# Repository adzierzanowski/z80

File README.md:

# Zilog Z80 playground

This is a scratchpad repository containing my Z80 sandbox.

## Assembler
The most interesting for other people is most probably **[an assembler](z80asm)**
written in Python.

The assembler is more-than-two-pass assembler to make code more readable than
optimized.

I've also written a 2-pass Z80 assember in C which is much faster.
[Check it out here](https://github.com/adzierzanowski/zasm).

## Z80 Minicomputer

For now the other part of the project consists of:

* a main board with 10 MHz Zilog Z80 CPU and some LEDs,
* a RAM board with two 62256 SRAM chips, 32 kiB of memory each
  and 7-segment displays showing data and address bus state,
* a CLKMOD board acting as a clock and interrupt controller.

Implying the following specs:

```
- Up to 1 MHZ Z80 CPU (because of bottleneck that is CLKMOD which will
                       be replaced with a crystal oscillator)
- 64 kiB SRAM
- No external non-volatile memory
- No IO at the moment
```

At the moment I'm developing the new IO Controller and IO device modules:
* 128x160 TFT display module,
* PS/2 keyboard input module.

In the `legacy/` directory there are some IO controller files which I used
for communicating with the CPU via serial port and low-resolution VGA output.

# Files

* `z80asm` – Python dual-syntax (i8080, Z80) assembler/disassembler module

* `busctl/` – Bus controller (and RAM Uploader)
* `clkmod/` – Clock emulator
* `fontmaker/` – Little HTML/JS utility for creating fonts
* `legacy/` – Old unused controllers
* `lib/` – ASM libraries
* `schematics/` – KiCAD schematics
* `static/` and `templates/` – Flask assets
* `tft` – TFT Display Controller

* `ctl.py` – Flask GUI for the clock emulator
* `prog.py` – Bus controller RAM programming interface
* `serialprompt.py` – Utility for fast testing of serial communication

# Resources

* https://maker.pro/pic/projects/z80-computer-project-part-1-the-cpu
* https://istvannovak.net/2018/01/25/zx-spectrum-ide-part-3-a-brief-overview-of-the-z80a-cpu/

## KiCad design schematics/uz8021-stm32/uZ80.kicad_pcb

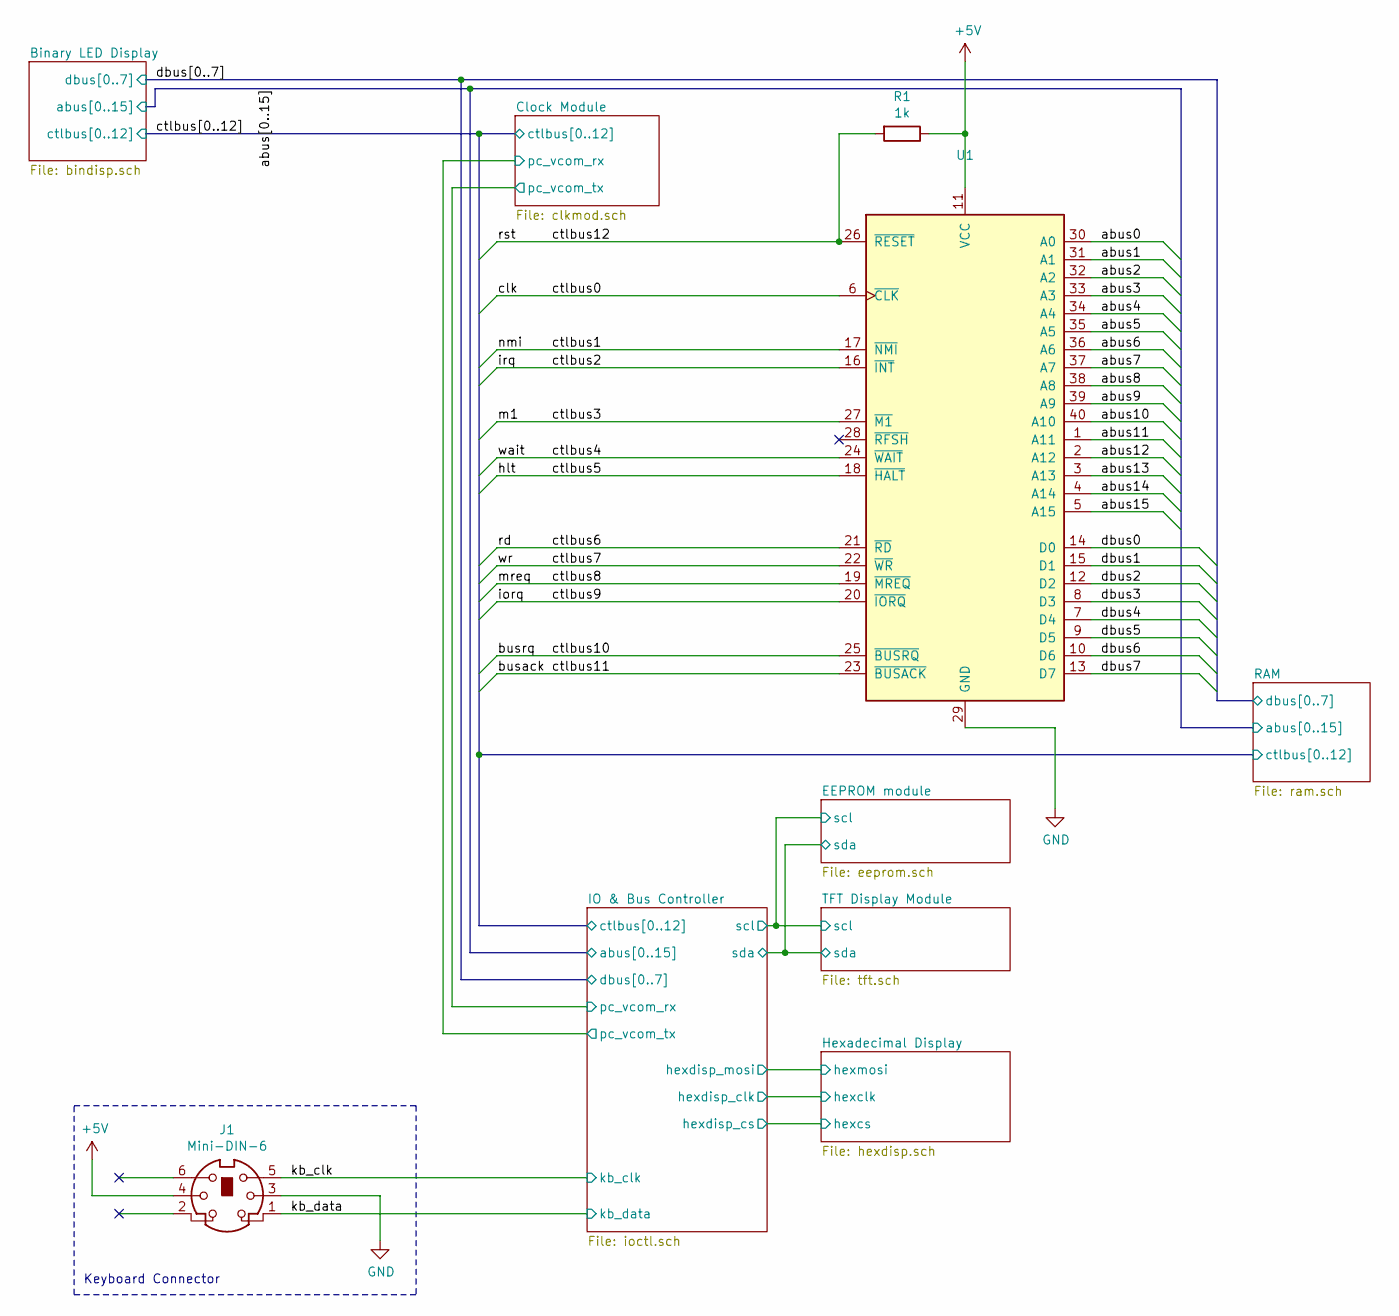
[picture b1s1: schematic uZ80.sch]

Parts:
J1: Mini-DIN-6; PinHeader_1x06_P2.54mm_Vertical
R1: 1k; R_0603_1608Metric_Pad0.98x0.95mm_HandSolder
U1: Z80CPU; DIP-40_W15.24mm_LongPads

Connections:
+5V: J1.4, R1.1, U1.11 (VCC); also elsewhere on the board
/abus0: U1.30 (A0); also elsewhere on the board
/abus1: U1.31 (A1); also elsewhere on the board
/abus2: U1.32 (A2); also elsewhere on the board
/abus3: U1.33 (A3); also elsewhere on the board
/abus4: U1.34 (A4); also elsewhere on the board
/abus5: U1.35 (A5); also elsewhere on the board
/abus6: U1.36 (A6); also elsewhere on the board
/abus7: U1.37 (A7); also elsewhere on the board
/abus8: U1.38 (A8); also elsewhere on the board
/abus9: U1.39 (A9); also elsewhere on the board
/abus10: U1.40 (A10); also elsewhere on the board
/abus11: U1.1 (A11); also elsewhere on the board
/abus12: U1.2 (A12); also elsewhere on the board
/abus13: U1.3 (A13); also elsewhere on the board
/abus14: U1.4 (A14); also elsewhere on the board
/abus15: U1.5 (A15); also elsewhere on the board
/busack: U1.23 (~BUSACK~); also elsewhere on the board
/busrq: U1.25 (~BUSRQ~); also elsewhere on the board
/clk: U1.6 (~CLK~); also elsewhere on the board
/ctlbus1: U1.17 (~NMI~); also elsewhere on the board
/ctlbus2: U1.16 (~INT~); also elsewhere on the board
/ctlbus3: U1.27 (~M1~); also elsewhere on the board
/ctlbus4: U1.24 (~WAIT~); also elsewhere on the board
/ctlbus5: U1.18 (~HALT~); also elsewhere on the board
/ctlbus6: U1.21 (~RD~); also elsewhere on the board
/ctlbus7: U1.22 (~WR~); also elsewhere on the board
/ctlbus8: U1.19 (~MREQ~); also elsewhere on the board
/ctlbus9: U1.20 (~IORQ~); also elsewhere on the board
/ctlbus12: R1.2, U1.26 (~RESET~); also elsewhere on the board
/dbus0: U1.14 (D0); also elsewhere on the board
/dbus1: U1.15 (D1); also elsewhere on the board
/dbus2: U1.12 (D2); also elsewhere on the board
/dbus3: U1.8 (D3); also elsewhere on the board
/dbus4: U1.7 (D4); also elsewhere on the board
/dbus5: U1.9 (D5); also elsewhere on the board
/dbus6: U1.10 (D6); also elsewhere on the board
/dbus7: U1.13 (D7); also elsewhere on the board
/kb_clk: J1.5; also elsewhere on the board
/kb_data: J1.1; also elsewhere on the board
GND: J1.3, U1.29 (GND); also elsewhere on the board

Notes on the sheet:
Keyboard Connector

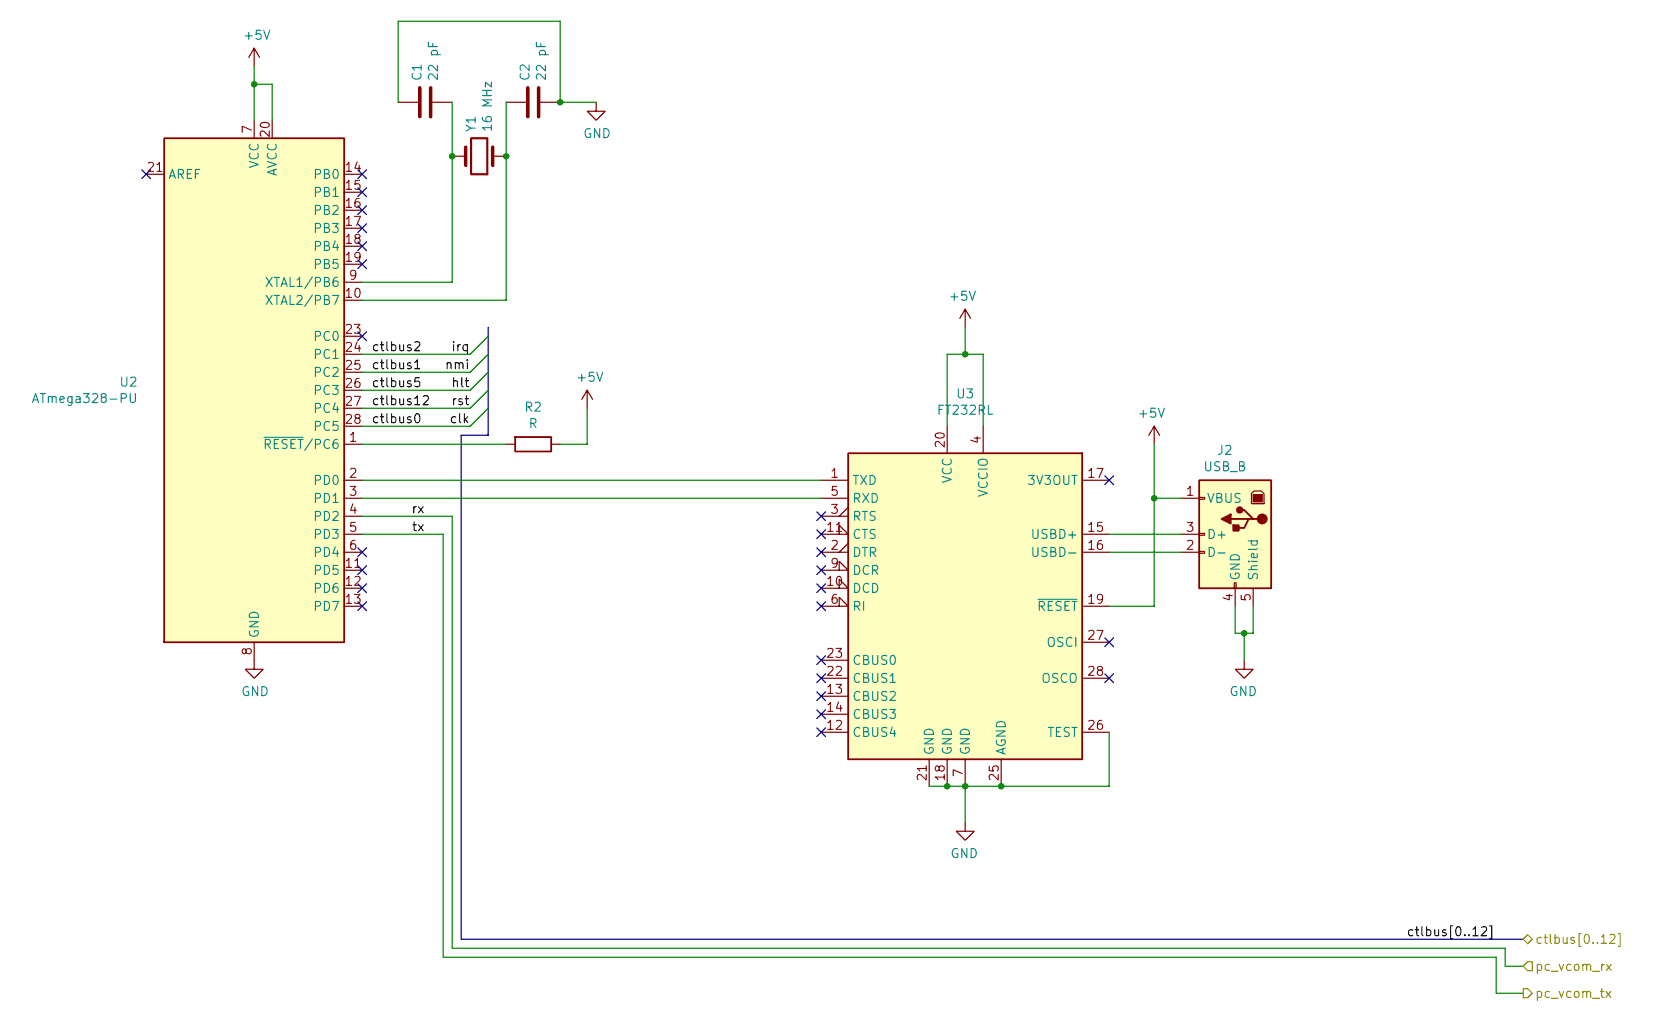
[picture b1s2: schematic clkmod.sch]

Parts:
C1, C2: 22 pF; C_0603_1608Metric_Pad1.08x0.95mm_HandSolder
J2: USB_B; USB_B_Lumberg_2411_02_Horizontal
R2: R; R_0603_1608Metric_Pad0.98x0.95mm_HandSolder
U2: ATmega328-PU; DIP-28_W7.62mm
U3: FT232RL; SSOP-28_5.3x10.2mm_P0.65mm
Y1: 16 MHz; Resonator-2Pin_W7.0mm_H2.5mm

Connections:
+5V: J2.1 (VBUS), R2.1, U2.7 (VCC), U2.20 (AVCC), U3.4 (VCCIO), U3.19 (~RESET~), U3.20 (VCC); also elsewhere on the board
/Clock Module/pc_vcom_rx: U2.4 (PD2); also elsewhere on the board
/IO & Bus Controller/pc_vcom_rx: U2.5 (PD3); also elsewhere on the board
/clk: U2.28 (PC5); also elsewhere on the board
/ctlbus1: U2.25 (PC2); also elsewhere on the board
/ctlbus2: U2.24 (PC1); also elsewhere on the board
/ctlbus5: U2.26 (PC3); also elsewhere on the board
/ctlbus12: U2.27 (PC4); also elsewhere on the board
GND: C1.1, C2.2, J2.4 (GND), J2.5 (Shield), U2.8 (GND), U2.22 (GND), U3.7 (GND), U3.18 (GND), U3.21 (GND), U3.25 (AGND), U3.26 (TEST); also elsewhere on the board
unnamed: C1.2, U2.9 (XTAL1/PB6), Y1.2
unnamed: C2.1, U2.10 (XTAL2/PB7), Y1.1
unnamed: J2.2 (D-), U3.16 (USBD-)
unnamed: J2.3 (D+), U3.15 (USBD+)
unnamed: R2.2, U2.1 (~RESET~/PC6)
unnamed: U2.2 (PD0), U3.1 (TXD)
unnamed: U2.3 (PD1), U3.5 (RXD)

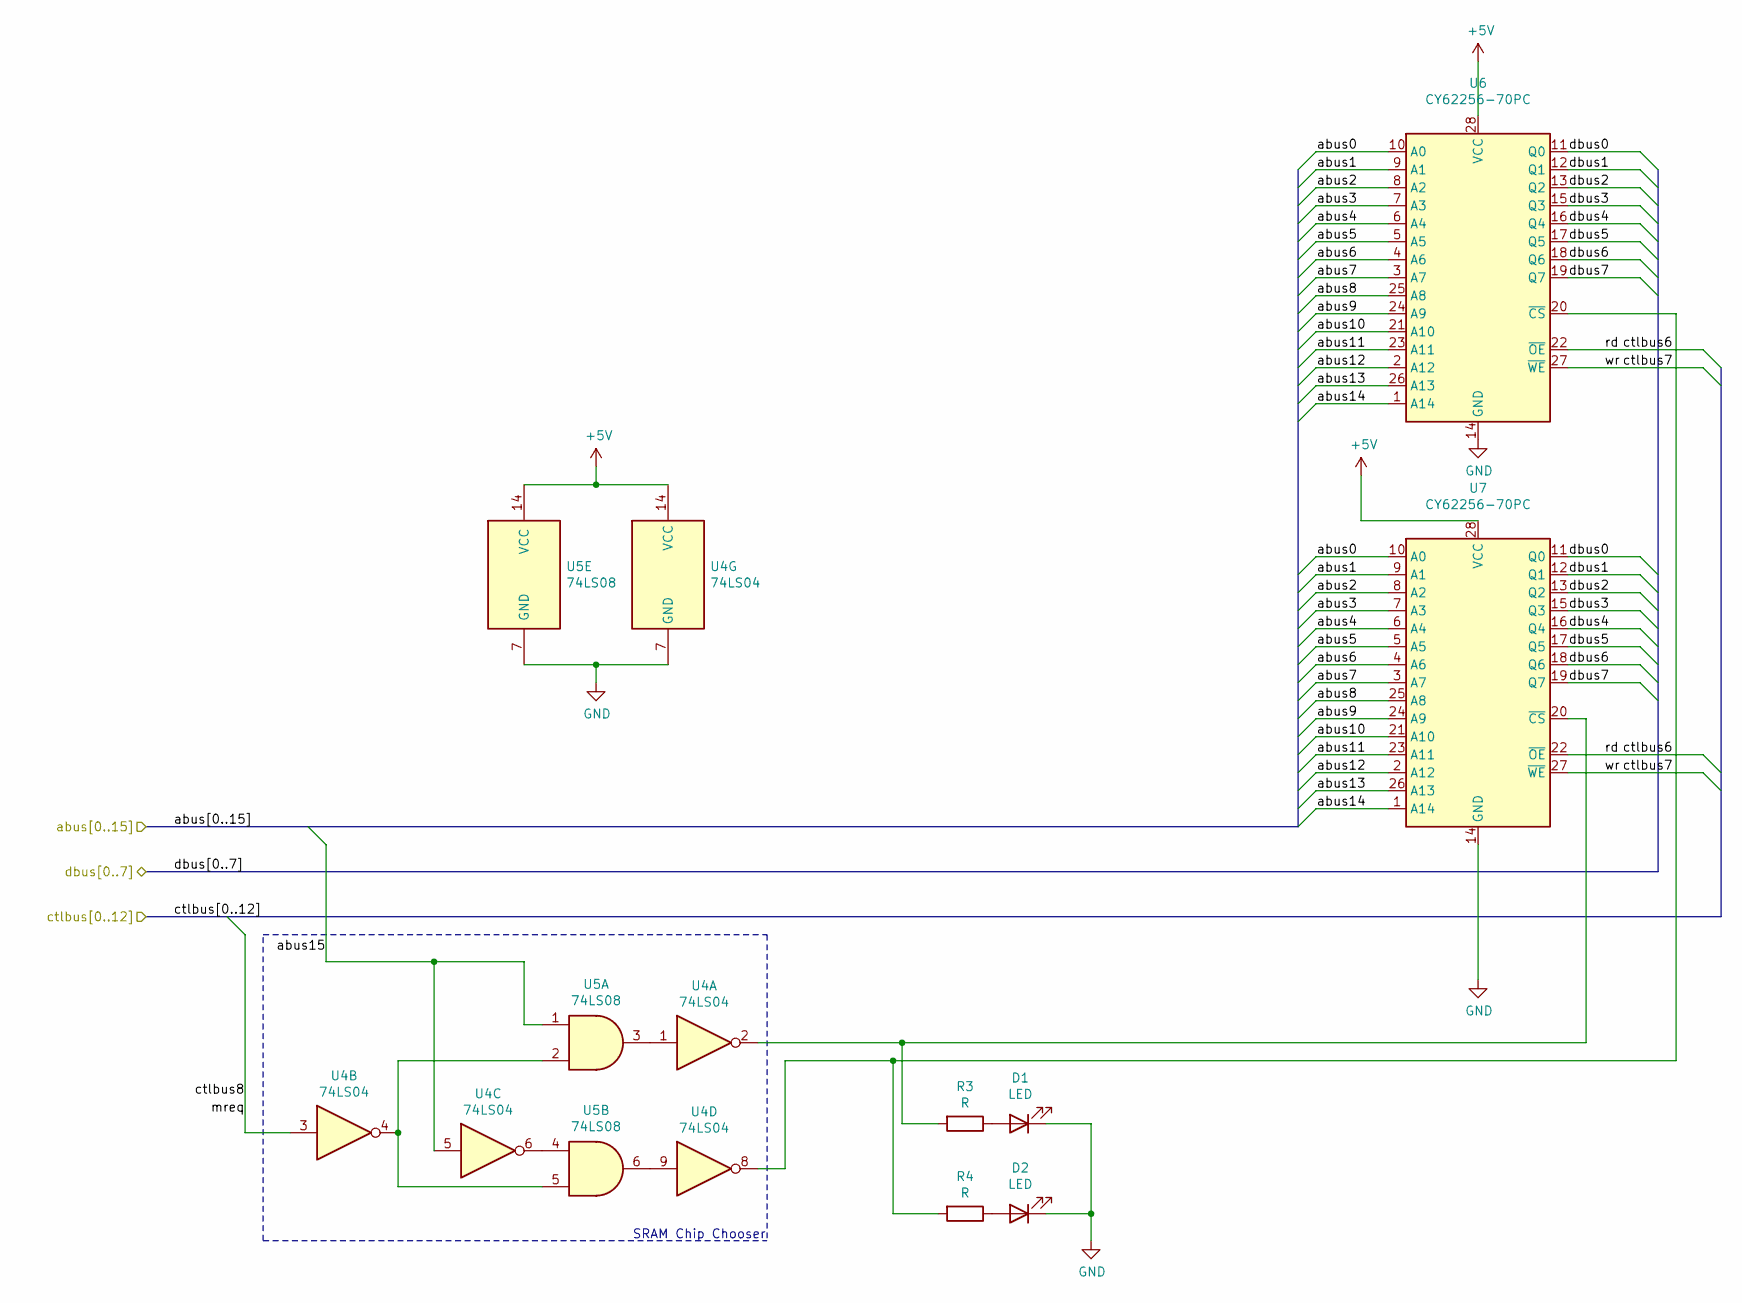
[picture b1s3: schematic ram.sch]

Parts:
D1, D2: LED; D_0603_1608Metric
R3, R4: R; R_0603_1608Metric_Pad0.98x0.95mm_HandSolder
U4: 74LS04; DIP-14_W7.62mm_LongPads
U5: 74LS08; DIP-14_W7.62mm_Socket_LongPads
U6, U7: CY62256-70PC; DIP-28_W15.24mm

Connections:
+5V: U4.14 (VCC), U5.14 (VCC), U6.28 (VCC), U7.28 (VCC); also elsewhere on the board
/abus0: U6.10 (A0), U7.10 (A0); also elsewhere on the board
/abus1: U6.9 (A1), U7.9 (A1); also elsewhere on the board
/abus2: U6.8 (A2), U7.8 (A2); also elsewhere on the board
/abus3: U6.7 (A3), U7.7 (A3); also elsewhere on the board
/abus4: U6.6 (A4), U7.6 (A4); also elsewhere on the board
/abus5: U6.5 (A5), U7.5 (A5); also elsewhere on the board
/abus6: U6.4 (A6), U7.4 (A6); also elsewhere on the board
/abus7: U6.3 (A7), U7.3 (A7); also elsewhere on the board
/abus8: U6.25 (A8), U7.25 (A8); also elsewhere on the board
/abus9: U6.24 (A9), U7.24 (A9); also elsewhere on the board
/abus10: U6.21 (A10), U7.21 (A10); also elsewhere on the board
/abus11: U6.23 (A11), U7.23 (A11); also elsewhere on the board
/abus12: U6.2 (A12), U7.2 (A12); also elsewhere on the board
/abus13: U6.26 (A13), U7.26 (A13); also elsewhere on the board
/abus14: U6.1 (A14), U7.1 (A14); also elsewhere on the board
/abus15: U4.5, U5.1; also elsewhere on the board
/ctlbus6: U6.22 (~OE), U7.22 (~OE); also elsewhere on the board
/ctlbus7: U6.27 (~WE), U7.27 (~WE); also elsewhere on the board
/ctlbus8: U4.3; also elsewhere on the board
/dbus0: U6.11 (Q0), U7.11 (Q0); also elsewhere on the board
/dbus1: U6.12 (Q1), U7.12 (Q1); also elsewhere on the board
/dbus2: U6.13 (Q2), U7.13 (Q2); also elsewhere on the board
/dbus3: U6.15 (Q3), U7.15 (Q3); also elsewhere on the board
/dbus4: U6.16 (Q4), U7.16 (Q4); also elsewhere on the board
/dbus5: U6.17 (Q5), U7.17 (Q5); also elsewhere on the board
/dbus6: U6.18 (Q6), U7.18 (Q6); also elsewhere on the board
/dbus7: U6.19 (Q7), U7.19 (Q7); also elsewhere on the board
GND: D1.1 (K), D2.1 (K), U4.7 (GND), U5.7 (GND), U6.14 (GND), U7.14 (GND); also elsewhere on the board
unnamed: D1.2 (A), R3.1
unnamed: D2.2 (A), R4.1
unnamed: R3.2, U4.2, U7.20 (~CS)
unnamed: R4.2, U4.8, U6.20 (~CS)
unnamed: U4.1, U5.3
unnamed: U4.4, U5.2, U5.5
unnamed: U4.6, U5.4
unnamed: U4.9, U5.6

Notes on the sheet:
SRAM Chip Chooser

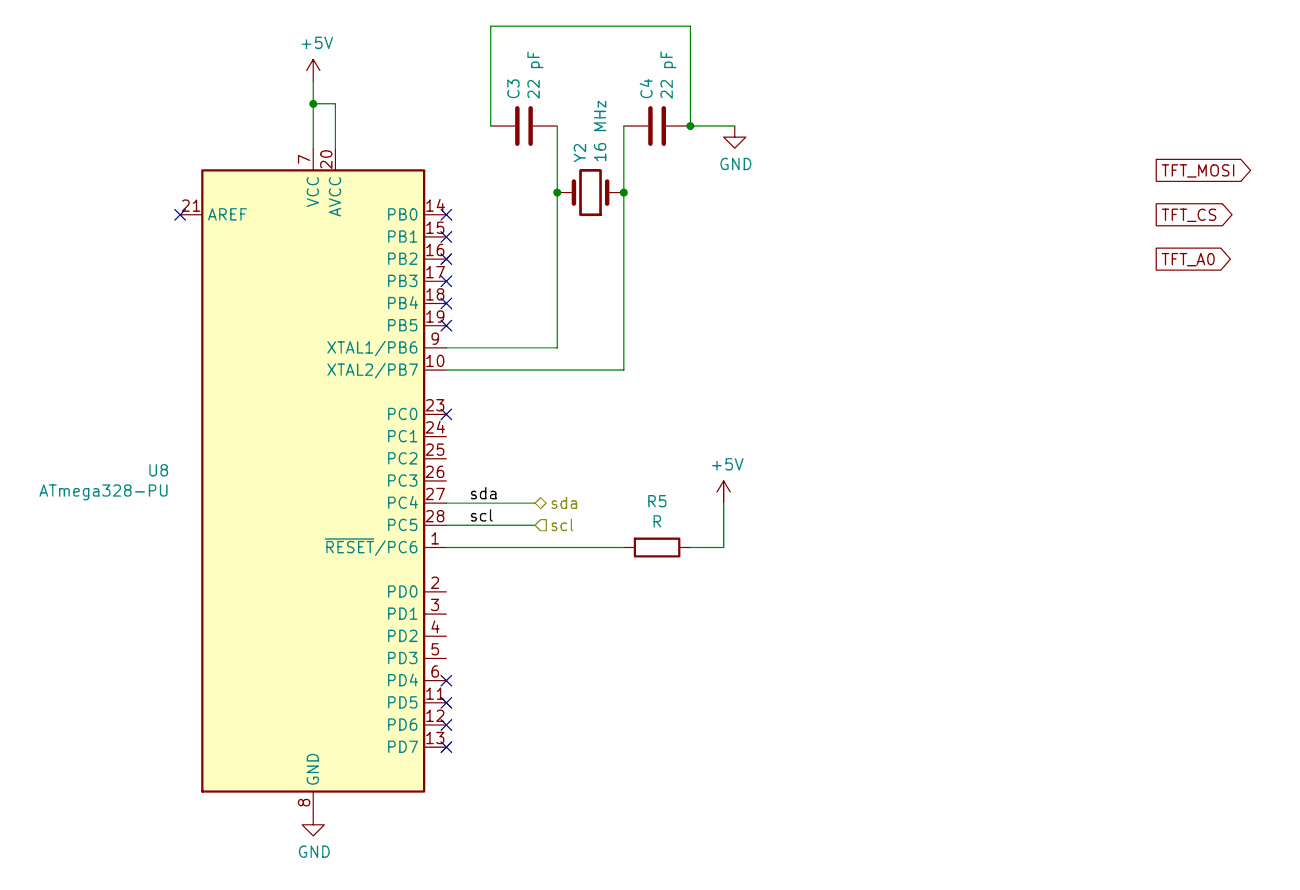
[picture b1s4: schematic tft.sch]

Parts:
C3, C4: 22 pF; C_0603_1608Metric_Pad1.08x0.95mm_HandSolder
R5: R; R_0603_1608Metric_Pad0.98x0.95mm_HandSolder
U8: ATmega328-PU; DIP-28_W7.62mm
Y2: 16 MHz; Resonator-2Pin_W7.0mm_H2.5mm

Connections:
+5V: R5.1, U8.7 (VCC), U8.20 (AVCC); also elsewhere on the board
/EEPROM module/scl: U8.28 (PC5); also elsewhere on the board
/EEPROM module/sda: U8.27 (PC4); also elsewhere on the board
GND: C3.1, C4.2, U8.8 (GND), U8.22 (GND); also elsewhere on the board
unnamed: C3.2, U8.9 (XTAL1/PB6), Y2.2
unnamed: C4.1, U8.10 (XTAL2/PB7), Y2.1
unnamed: R5.2, U8.1 (~RESET~/PC6)

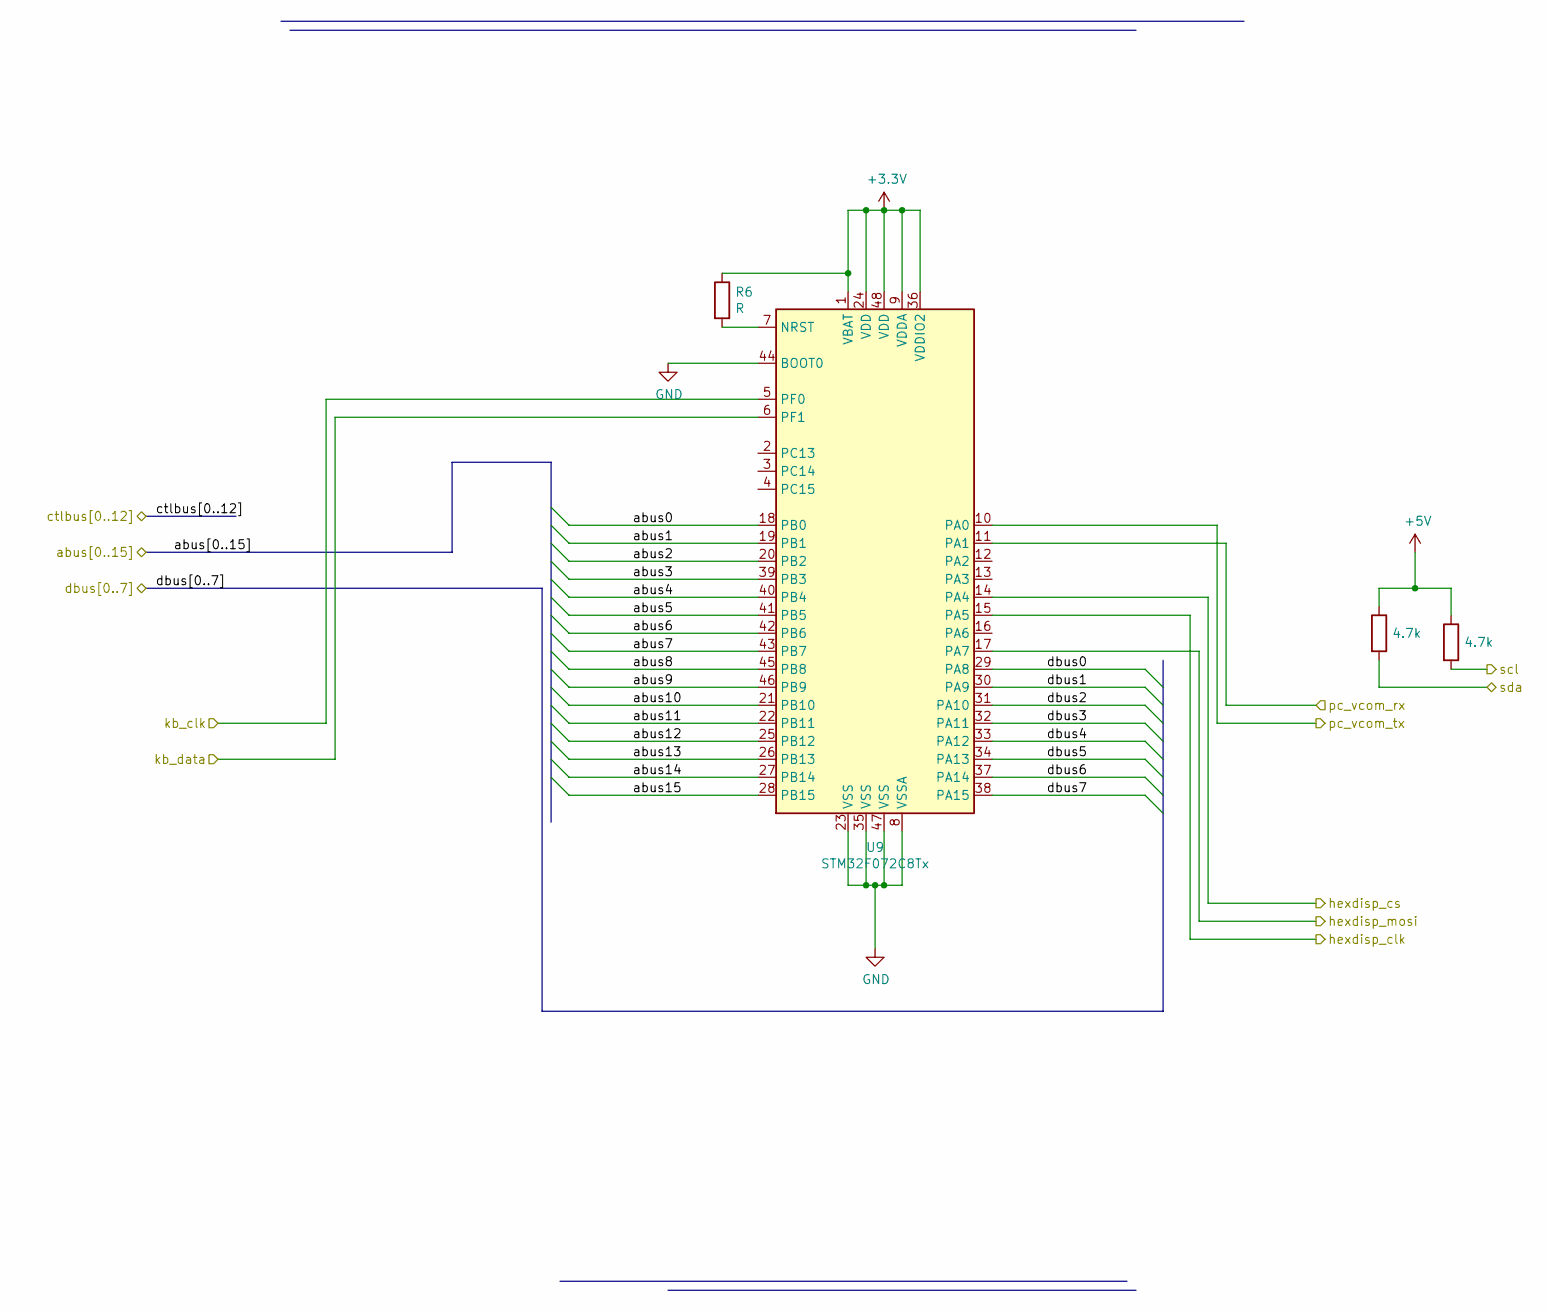
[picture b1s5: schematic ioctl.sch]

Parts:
R6: R; R_0603_1608Metric_Pad0.98x0.95mm_HandSolder
R7, R8: 4.7k; R_0402_1005Metric_Pad0.72x0.64mm_HandSolder
U9: STM32F072C8Tx; LQFP-48_7x7mm_P0.5mm

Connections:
+3V3: R6.1, U9.1 (VBAT), U9.9 (VDDA), U9.24 (VDD), U9.36 (VDDIO2), U9.48 (VDD)
+5V: R7.1, R8.1; also elsewhere on the board
/Clock Module/pc_vcom_rx: U9.10 (PA0); also elsewhere on the board
/EEPROM module/scl: R8.2; also elsewhere on the board
/EEPROM module/sda: R7.2; also elsewhere on the board
/Hexadecimal Display/hexclk: U9.15 (PA5); also elsewhere on the board
/Hexadecimal Display/hexcs: U9.14 (PA4); also elsewhere on the board
/IO & Bus Controller/hexdisp_mosi: U9.17 (PA7); also elsewhere on the board
/IO & Bus Controller/pc_vcom_rx: U9.11 (PA1); also elsewhere on the board
/abus0: U9.18 (PB0); also elsewhere on the board
/abus1: U9.19 (PB1); also elsewhere on the board
/abus2: U9.20 (PB2); also elsewhere on the board
/abus3: U9.39 (PB3); also elsewhere on the board
/abus4: U9.40 (PB4); also elsewhere on the board
/abus5: U9.41 (PB5); also elsewhere on the board
/abus6: U9.42 (PB6); also elsewhere on the board
/abus7: U9.43 (PB7); also elsewhere on the board
/abus8: U9.45 (PB8); also elsewhere on the board
/abus9: U9.46 (PB9); also elsewhere on the board
/abus10: U9.21 (PB10); also elsewhere on the board
/abus11: U9.22 (PB11); also elsewhere on the board
/abus12: U9.25 (PB12); also elsewhere on the board
/abus13: U9.26 (PB13); also elsewhere on the board
/abus14: U9.27 (PB14); also elsewhere on the board
/abus15: U9.28 (PB15); also elsewhere on the board
/dbus0: U9.29 (PA8); also elsewhere on the board
/dbus1: U9.30 (PA9); also elsewhere on the board
/dbus2: U9.31 (PA10); also elsewhere on the board
/dbus3: U9.32 (PA11); also elsewhere on the board
/dbus4: U9.33 (PA12); also elsewhere on the board
/dbus5: U9.34 (PA13); also elsewhere on the board
/dbus6: U9.37 (PA14); also elsewhere on the board
/dbus7: U9.38 (PA15); also elsewhere on the board
/kb_clk: U9.5 (PF0); also elsewhere on the board
/kb_data: U9.6 (PF1); also elsewhere on the board
GND: U9.8 (VSSA), U9.23 (VSS), U9.35 (VSS), U9.44 (BOOT0), U9.47 (VSS); also elsewhere on the board
unnamed: R6.2, U9.7 (NRST)

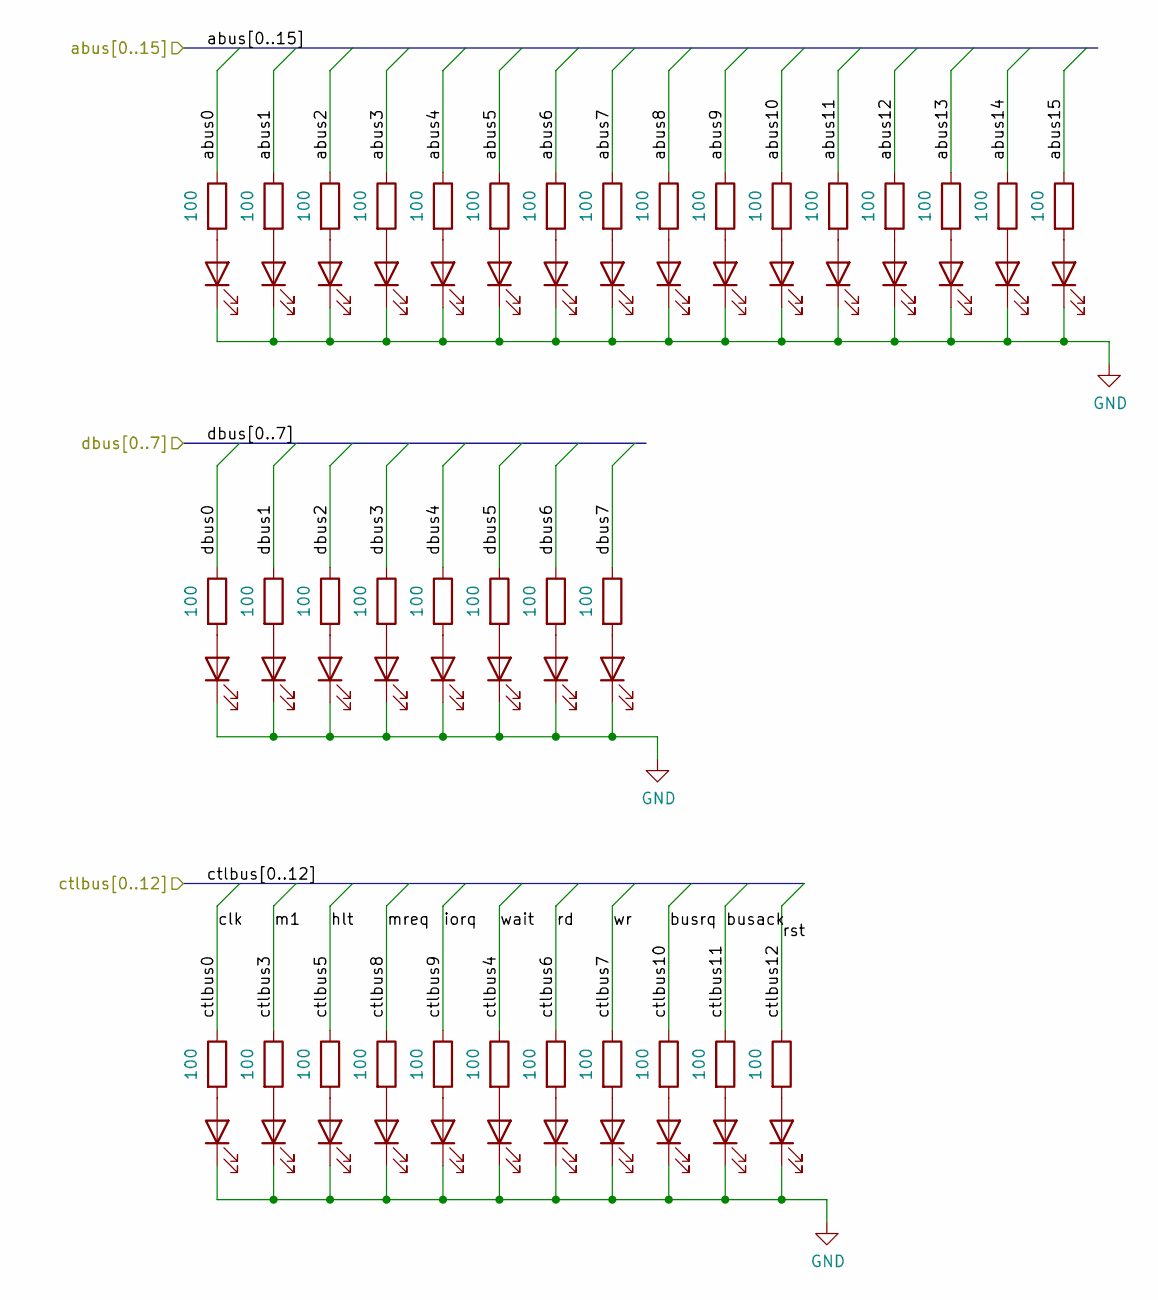
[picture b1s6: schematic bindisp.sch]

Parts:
D3, D4, D5, D6, D7, D8, D9, D10, D11, D12, D13, D14, D15, D16, D17, D18, D19, D20, D21, D22, D23, D24, D25, D26, D27, D28, D29, D30, D31, D32, D33, D34, D35, D36, D37: LED; D_0603_1608Metric
R9, R10, R11, R12, R13, R14, R15, R16, R17, R18, R19, R20, R21, R22, R23, R24, R25, R26, R27, R28, R29, R30, R31, R32, R33, R34, R35, R36, R37, R38, R39, R40, R41, R42, R43: 100; R_0603_1608Metric_Pad0.98x0.95mm_HandSolder

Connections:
/abus0: R9.1; also elsewhere on the board
/abus1: R12.1; also elsewhere on the board
/abus2: R15.1; also elsewhere on the board
/abus3: R18.1; also elsewhere on the board
/abus4: R21.1; also elsewhere on the board
/abus5: R24.1; also elsewhere on the board
/abus6: R27.1; also elsewhere on the board
/abus7: R30.1; also elsewhere on the board
/abus8: R33.1; also elsewhere on the board
/abus9: R35.1; also elsewhere on the board
/abus10: R37.1; also elsewhere on the board
/abus11: R39.1; also elsewhere on the board
/abus12: R40.1; also elsewhere on the board
/abus13: R41.1; also elsewhere on the board
/abus14: R42.1; also elsewhere on the board
/abus15: R43.1; also elsewhere on the board
/busack: R36.1; also elsewhere on the board
/busrq: R34.1; also elsewhere on the board
/clk: R11.1; also elsewhere on the board
/ctlbus3: R14.1; also elsewhere on the board
/ctlbus4: R26.1; also elsewhere on the board
/ctlbus5: R17.1; also elsewhere on the board
/ctlbus6: R29.1; also elsewhere on the board
/ctlbus7: R32.1; also elsewhere on the board
/ctlbus8: R20.1; also elsewhere on the board
/ctlbus9: R23.1; also elsewhere on the board
/ctlbus12: R38.1; also elsewhere on the board
/dbus0: R10.1; also elsewhere on the board
/dbus1: R13.1; also elsewhere on the board
/dbus2: R16.1; also elsewhere on the board
/dbus3: R19.1; also elsewhere on the board
/dbus4: R22.1; also elsewhere on the board
/dbus5: R25.1; also elsewhere on the board
/dbus6: R28.1; also elsewhere on the board
/dbus7: R31.1; also elsewhere on the board
GND: D3.1 (K), D4.1 (K), D5.1 (K), D6.1 (K), D7.1 (K), D8.1 (K), D9.1 (K), D10.1 (K), D11.1 (K), D12.1 (K), D13.1 (K), D14.1 (K), D15.1 (K), D16.1 (K), D17.1 (K), D18.1 (K), D19.1 (K), D20.1 (K), D21.1 (K), D22.1 (K), D23.1 (K), D24.1 (K), D25.1 (K), D26.1 (K), D27.1 (K), D28.1 (K), D29.1 (K), D30.1 (K), D31.1 (K), D32.1 (K), D33.1 (K), D34.1 (K), D35.1 (K), D36.1 (K), D37.1 (K); also elsewhere on the board
unnamed: D3.2 (A), R9.2
unnamed: D4.2 (A), R10.2
unnamed: D5.2 (A), R11.2
unnamed: D6.2 (A), R12.2
unnamed: D7.2 (A), R13.2
unnamed: D8.2 (A), R14.2
unnamed: D9.2 (A), R15.2
unnamed: D10.2 (A), R16.2
unnamed: D11.2 (A), R17.2
unnamed: D12.2 (A), R18.2
unnamed: D13.2 (A), R19.2
unnamed: D14.2 (A), R20.2
unnamed: D15.2 (A), R21.2
unnamed: D16.2 (A), R22.2
unnamed: D17.2 (A), R23.2
unnamed: D18.2 (A), R24.2
unnamed: D19.2 (A), R25.2
unnamed: D20.2 (A), R26.2
unnamed: D21.2 (A), R27.2
unnamed: D22.2 (A), R28.2
unnamed: D23.2 (A), R29.2
unnamed: D24.2 (A), R30.2
unnamed: D25.2 (A), R31.2
unnamed: D26.2 (A), R32.2
unnamed: D27.2 (A), R33.2
unnamed: D28.2 (A), R34.2
unnamed: D29.2 (A), R35.2
unnamed: D30.2 (A), R36.2
unnamed: D31.2 (A), R37.2
unnamed: D32.2 (A), R38.2
unnamed: D33.2 (A), R39.2
unnamed: D34.2 (A), R40.2
unnamed: D35.2 (A), R41.2
unnamed: D36.2 (A), R42.2
unnamed: D37.2 (A), R43.2

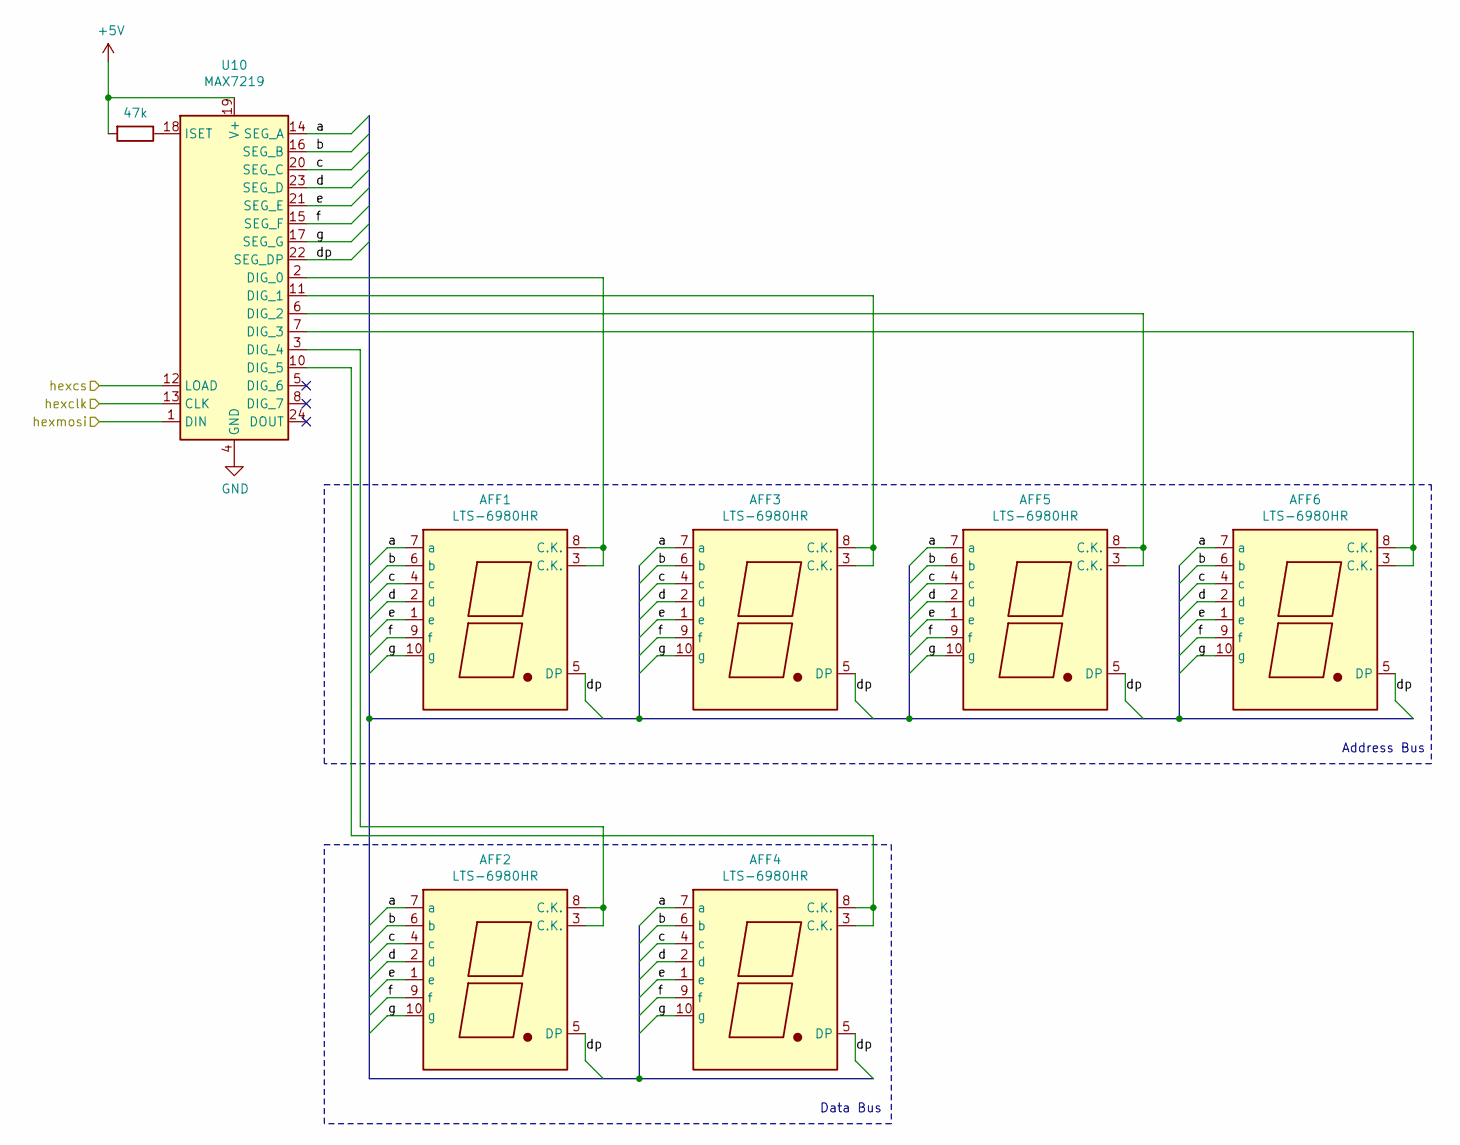
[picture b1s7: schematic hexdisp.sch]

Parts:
AFF1, AFF2, AFF3, AFF4, AFF5, AFF6: LTS-6980HR; 7SegmentLED_LTS6760_LTS6780
R44: 47k; R_0603_1608Metric_Pad0.98x0.95mm_HandSolder
U10: MAX7219; DIP-24_W7.62mm_Socket_LongPads

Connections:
+5V: R44.2, U10.19 (V+); also elsewhere on the board
/Hexadecimal Display/a: AFF1.7 (a), AFF2.7 (a), AFF3.7 (a), AFF4.7 (a), AFF5.7 (a), AFF6.7 (a), U10.14 (SEG_A)
/Hexadecimal Display/b: AFF1.6 (b), AFF2.6 (b), AFF3.6 (b), AFF4.6 (b), AFF5.6 (b), AFF6.6 (b), U10.16 (SEG_B)
/Hexadecimal Display/c: AFF1.4 (c), AFF2.4 (c), AFF3.4 (c), AFF4.4 (c), AFF5.4 (c), AFF6.4 (c), U10.20 (SEG_C)
/Hexadecimal Display/d: AFF1.2 (d), AFF2.2 (d), AFF3.2 (d), AFF4.2 (d), AFF5.2 (d), AFF6.2 (d), U10.23 (SEG_D)
/Hexadecimal Display/dp: AFF1.5 (DP), AFF2.5 (DP), AFF3.5 (DP), AFF4.5 (DP), AFF5.5 (DP), AFF6.5 (DP), U10.22 (SEG_DP)
/Hexadecimal Display/e: AFF1.1 (e), AFF2.1 (e), AFF3.1 (e), AFF4.1 (e), AFF5.1 (e), AFF6.1 (e), U10.21 (SEG_E)
/Hexadecimal Display/f: AFF1.9 (f), AFF2.9 (f), AFF3.9 (f), AFF4.9 (f), AFF5.9 (f), AFF6.9 (f), U10.15 (SEG_F)
/Hexadecimal Display/g: AFF1.10 (g), AFF2.10 (g), AFF3.10 (g), AFF4.10 (g), AFF5.10 (g), AFF6.10 (g), U10.17 (SEG_G)
/Hexadecimal Display/hexclk: U10.13 (CLK); also elsewhere on the board
/Hexadecimal Display/hexcs: U10.12 (LOAD); also elsewhere on the board
/IO & Bus Controller/hexdisp_mosi: U10.1 (DIN); also elsewhere on the board
GND: U10.4 (GND), U10.9 (GND); also elsewhere on the board
unnamed: AFF1.3 (C.K.), AFF1.8 (C.K.), U10.2 (DIG_0)
unnamed: AFF2.3 (C.K.), AFF2.8 (C.K.), U10.3 (DIG_4)
unnamed: AFF3.3 (C.K.), AFF3.8 (C.K.), U10.11 (DIG_1)
unnamed: AFF4.3 (C.K.), AFF4.8 (C.K.), U10.10 (DIG_5)
unnamed: AFF5.3 (C.K.), AFF5.8 (C.K.), U10.6 (DIG_2)
unnamed: AFF6.3 (C.K.), AFF6.8 (C.K.), U10.7 (DIG_3)
unnamed: R44.1, U10.18 (ISET)

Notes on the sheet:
Address Bus
Data Bus

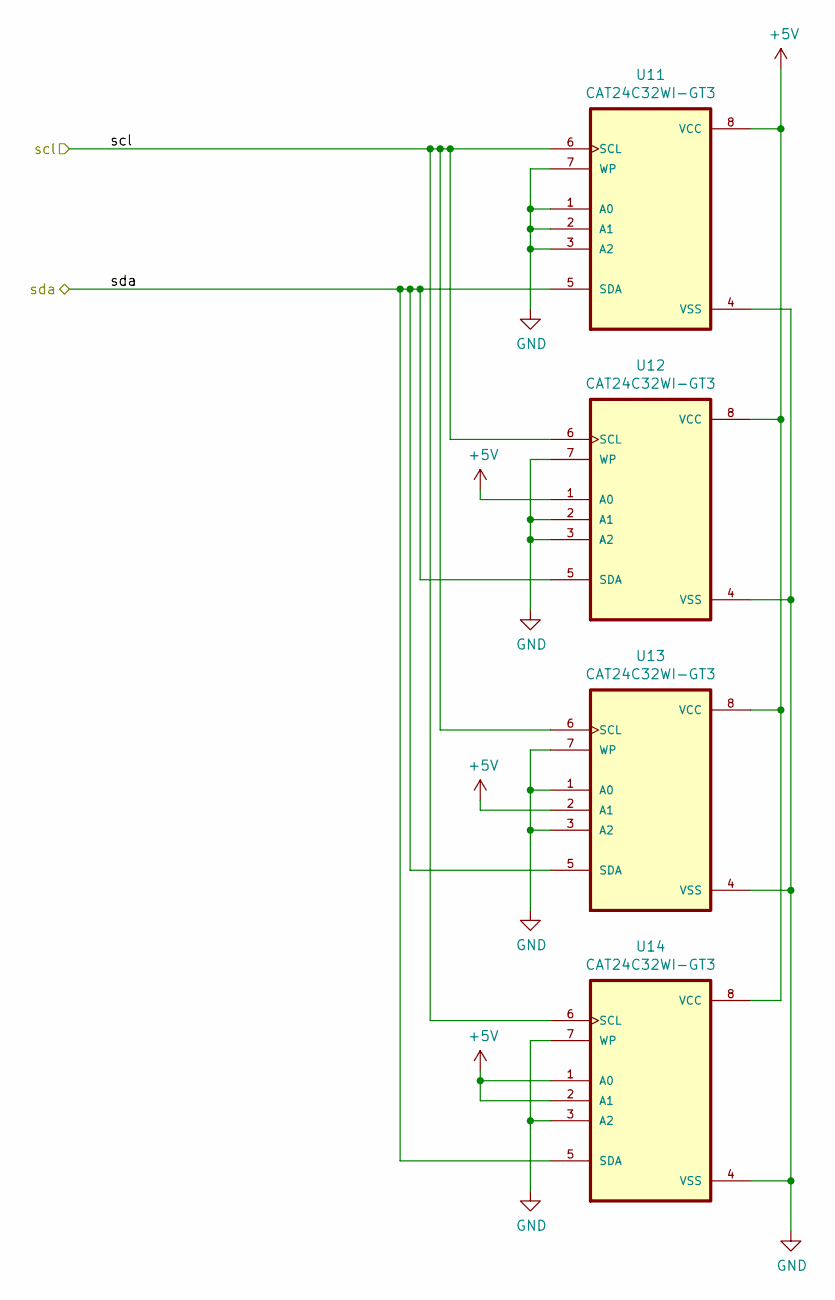
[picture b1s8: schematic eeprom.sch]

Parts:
U11, U12, U13, U14: CAT24C32WI-GT3; SOIC127P600X175-8N

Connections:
+5V: U11.8 (VCC), U12.1 (A0), U12.8 (VCC), U13.2 (A1), U13.8 (VCC), U14.1 (A0), U14.2 (A1), U14.8 (VCC); also elsewhere on the board
/EEPROM module/scl: U11.6 (SCL), U12.6 (SCL), U13.6 (SCL), U14.6 (SCL); also elsewhere on the board
/EEPROM module/sda: U11.5 (SDA), U12.5 (SDA), U13.5 (SDA), U14.5 (SDA); also elsewhere on the board
GND: U11.1 (A0), U11.2 (A1), U11.3 (A2), U11.4 (VSS), U11.7 (WP), U12.2 (A1), U12.3 (A2), U12.4 (VSS), U12.7 (WP), U13.1 (A0), U13.3 (A2), U13.4 (VSS), U13.7 (WP), U14.3 (A2), U14.4 (VSS), U14.7 (WP); also elsewhere on the board
